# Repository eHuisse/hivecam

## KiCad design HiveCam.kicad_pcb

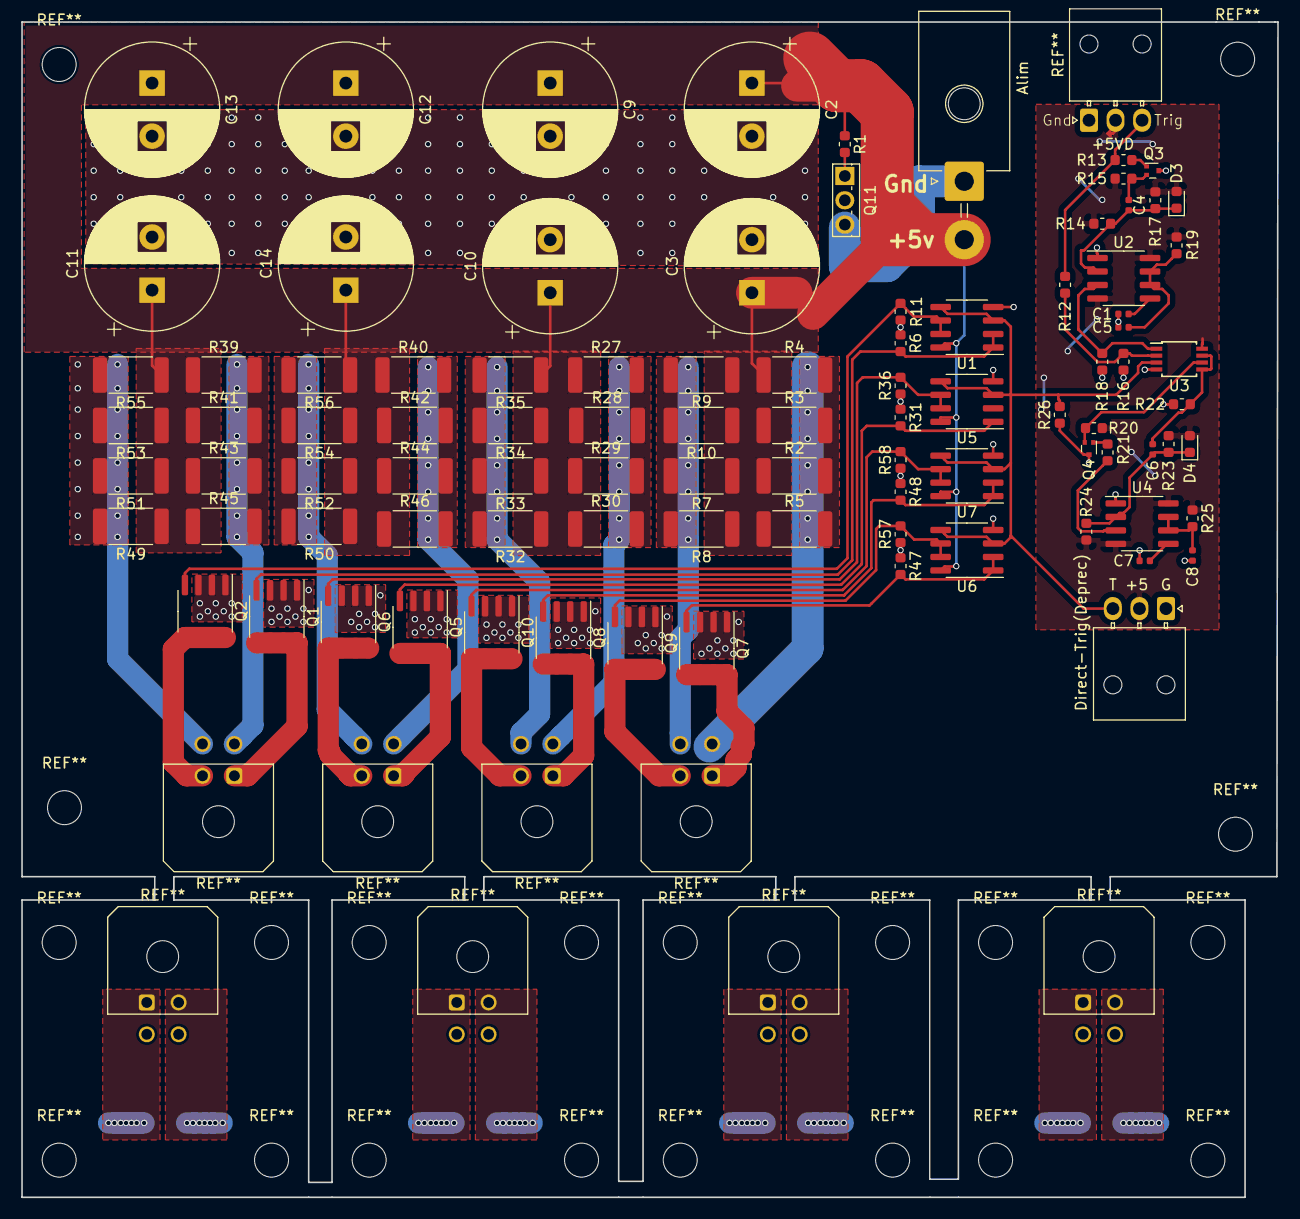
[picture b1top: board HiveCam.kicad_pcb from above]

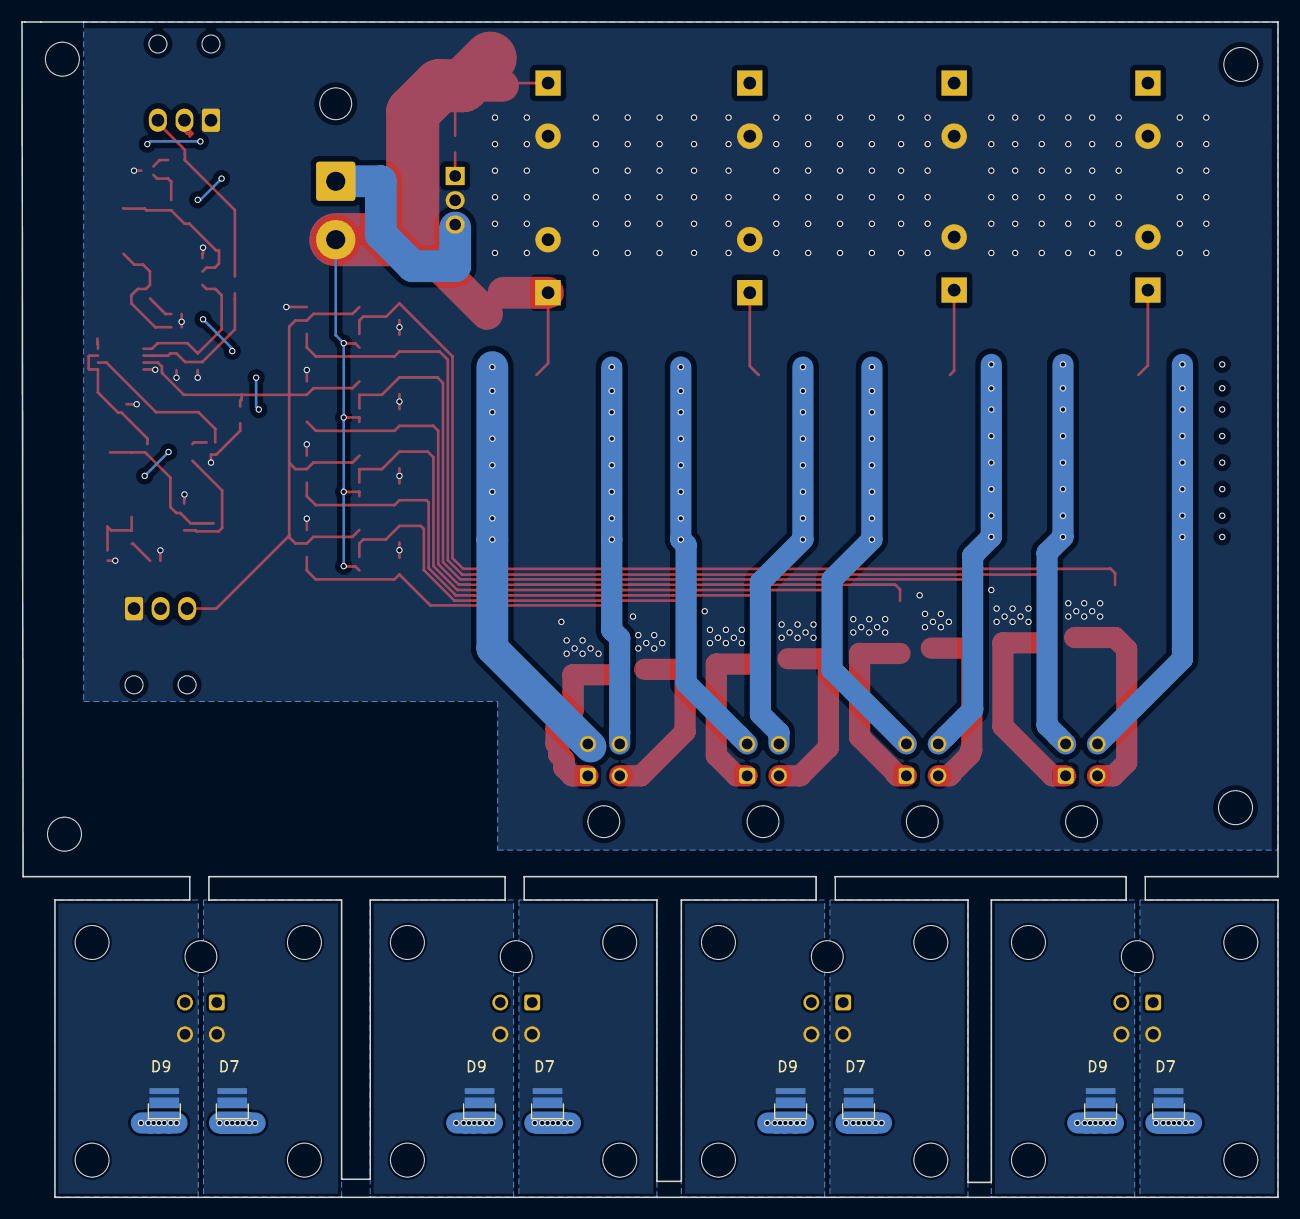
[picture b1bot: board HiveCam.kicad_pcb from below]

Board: 2 copper layers, 118.3 x 110.7 mm, 100 parts (8 on the bottom side), 38 nets.

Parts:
Alim: Molex_Mega-Fit_76825-0002_2x01_P5.70mm_Horizontal
C1, C7: 0.01u; C_0402_1005Metric
C2, C3, C9, C10, C11, C12, C13, C14: 2m; CP_Radial_D12.5mm_P5.00mm
C4, C5, C6, C8: 1u; C_0402_1005Metric
D3, D4: DIODE; D_0603_1608Metric
D7, D7#2, D7#3, D7#4, D9, D9#2, D9#3, D9#4: LED; SFH-4716S
Direct-Trig(Deprec): Molex_Nano-Fit_105313-xx03_1x03_P2.50mm_Horizontal
Q1, Q2, Q5, Q6, Q7, Q8, Q9, Q10: AO4752; SOIC-8_3.9x4.9mm_P1.27mm
Q3, Q4: NSVMMBT2222AM3T5G; SOT-723
Q11: RFD14N05L; TO-251-3_Vertical
R1, R6, R11, R12, R13, R16, R18, R21, R22, R26, R31, R36, R47, R48, R57, R58: 10k; R_0603_1608Metric
R2, R3, R4, R5, R7, R8, R9, R10, R27, R28, R29, R30, R32, R33, R34, R35, R39, R40, R41, R42, R43, R44, R45, R46, R49, R50, R51, R52, R53, R54, R55, R56: 2; R_2512_6332Metric
R14, R17, R23, R24: 22k; R_0603_1608Metric
R15, R20: 4.7k; R_0603_1608Metric
R19: 500; R_0603_1608Metric
R25: 100k; R_0603_1608Metric
U1, U5, U6, U7: LMV358; SOIC-8_3.9x4.9mm_P1.27mm
U2, U4: NE555DR; SOIC-8_3.9x4.9mm_P1.27mm
U3: 74LVC2G08; TSSOP-8_3x3mm_P0.65mm

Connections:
+5V: Alim.2, C2.1, C3.1, C9.1, C10.1, C11.1, C12.1, C13.1, C14.1, R1.1, R2.1, R3.1, R4.1, R5.1, R7.1, R8.1, R9.1, R10.1, R27.1, R28.1, R29.1, R30.1, R32.1, R33.1, R34.1, R35.1, R39.1, R40.1, R41.1, R42.1, R43.1, R44.1, R45.1, R46.1, R49.1, R50.1, R51.1, R52.1, R53.1, R54.1, R55.1, R56.1, U1.8, U5.8, U6.8, U7.8
+5vD: D3.2, D4.2, Direct-Trig(Deprec).2, R14.2, R15.1, R17.1, R19.1, R20.1, R23.1, R24.2, R25.1, U2.4, U2.8, U3.8, U4.4, U4.8
GND: Alim.1, Q11.3
GNDP: C1.2, C2.2, C3.2, C5.2, C7.2, C8.2, C9.2, C10.2, C11.2, C12.2, C13.2, C14.2, Direct-Trig(Deprec).1, Q1.1, Q1.2, Q1.3, Q2.1, Q2.2, Q2.3, Q3.3, Q4.3, Q5.1, Q5.2, Q5.3, Q6.1, Q6.2, Q6.3, Q7.1, Q7.2, Q7.3, Q8.1, Q8.2, Q8.3, Q9.1, Q9.2, Q9.3, Q10.1, Q10.2, Q10.3, Q11.2, R6.1, R11.1, R16.1, R18.1, R22.1, R26.1, R31.1, R36.1, R47.1, R48.1, R57.1, R58.1, U1.4, U2.1, U3.4, U4.1, U5.4, U6.4, U7.4
unnamed: C1.1, U2.5
unnamed: C4.1, D3.1, R14.1, R17.2, U2.2
unnamed: C4.2, Q3.2, R15.2
unnamed: C5.1, R19.2, U2.6, U2.7
unnamed: C6.1, D4.1, R23.2, R24.1, U4.2
unnamed: C6.2, R22.2, U3.5, U3.7
unnamed: C7.1, U4.5
unnamed: C8.1, R25.2, U4.6, U4.7
unnamed: D7#4.1, Q1.5
unnamed: R2.2, R3.2, R4.2, R5.2
unnamed: D9#4.1, Q2.5
unnamed: R7.2, R8.2, R9.2, R10.2
unnamed: R27.2, R28.2, R29.2, R30.2
unnamed: R32.2, R33.2, R34.2, R35.2
unnamed: D7#4.2, R39.2, R41.2, R43.2, R45.2
unnamed: R40.2, R42.2, R44.2, R46.2
unnamed: D9#4.2, R49.2, R51.2, R53.2, R55.2
unnamed: R50.2, R52.2, R54.2, R56.2
unnamed: Q1.4, R6.2, U1.1, U1.2
unnamed: Q2.4, R11.2, U1.6, U1.7
unnamed: Q3.1, R13.1
unnamed: Q4.1, R21.1
unnamed: Q4.2, R20.2, U3.6
unnamed: Q5.4, R31.2, U5.1, U5.2
unnamed: Q6.4, R36.2, U5.6, U5.7
unnamed: Q7.4, R47.2, U6.1, U6.2
unnamed: Q8.4, R48.2, U7.1, U7.2
unnamed: Q9.4, R57.2, U6.6, U6.7
unnamed: Q10.4, R58.2, U7.6, U7.7
unnamed: R12.2, R16.2, U3.2
unnamed: R18.2, U2.3, U3.1
unnamed: R21.2, U4.3
unnamed: Direct-Trig(Deprec).3, R26.2, U1.3, U1.5, U3.3, U5.3, U5.5, U6.3, U6.5, U7.3, U7.5
Trigger: R12.1, R13.2

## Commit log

2019-06-26 finished project
